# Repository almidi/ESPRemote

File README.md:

# ESPRemote
### VER 0.1

A simple WiFI remote controller using the ESP8266 SoC.

The goal of this project is the creation of a simple to use WiFi remote controller aimed at usage with the numerous home automation suites available, such as _[HomeAssistant](https://www.home-assistant.io)_ and _[OpenHab](https://www.openhab.org)_.

The system utilizes an _[Espressif ESP-12](https://docs.platformio.org/en/latest/boards/espressif8266/esp12e.html)_ module coupled with an _[MCP73831T](https://www.google.gr/url?sa=t&rct=j&q=&esrc=s&source=web&cd=1&ved=2ahUKEwiDvMTDpvbgAhXJfFAKHZEMD0UQFjAAegQIChAC&url=https%3A%2F%2Fwww.sparkfun.com%2Fdatasheets%2FPrototyping%2FBatteries%2FMCP73831T.pdf&usg=AOvVaw3YKAY2DJq01YtSUwFzsNai)_ chip for battery management and an _[AP2112K](https://www.google.gr/url?sa=t&rct=j&q=&esrc=s&source=web&cd=1&ved=2ahUKEwjnxLrnpvbgAhUEK1AKHWMBD-AQFjAAegQIChAC&url=https%3A%2F%2Fwww.diodes.com%2Fassets%2FDatasheets%2FAP2112.pdf&usg=AOvVaw2XV2W1VE0JfD3LlF0lkARI)_ LDO voltage regulator.

## Configurations

The board can be configured as a battery powered remote control, or as a DC powered button panel. To achieve this a jumper was added (SJ2) to select between battery and direct USB power. A second jumper was also added (JP2) to bypass the power switch. Using the above jumpers, the BMS circuit can be completely ignored and left unpopulated in case the device is inteded for always pluged-in use from a 5V DC power supply.

## Firmware

Using the _[Espressif ESP-12](https://docs.platformio.org/en/latest/boards/espressif8266/esp12e.html)_ module offers great flexibility in existing firmware options. Currently the _[ESPHome](https://esphome.io/index.html)_ firmware is used, designed for seemless intergation with the _[HomeAssistant](https://www.home-assistant.io)_ platform.

Due to the device not beign intended as a development board, an FTDI chip was excluded from the design, leaving the need for a small 6-pin SH 1.0mm micro jst connector as a UART interface.

**Uploading new firmware requires the pin D0 and GND of the UART connector to be tied together.** After doing so the device must be reset, setting it in download mode and enabling new firmware to be uploaded. **This can also be achieved holding down the 4th button before powering on the device**.

## I/O

|                 | Pin    |
|-----------------|--------|
| Button 1        | GPIO5  |
| Button 2        | GPIO4  |
| Button 3        | GPIO12 |
| Button 4        | GPIO0  |
| Button 5        | GPIO13 |
| Battery Voltage | ADC    |
| Status Led      | GPIO16 |

## PCB

## Enclosure

The enclosure is designed to incorporate a single 400mAh li-po cell and be 3D printed in two parts.

## Future Work

- Incorporate a small 128x64 OLED screen.
- Add an IR transmitter to the design, so that the controller can be used with existing household devices.
- Add an accelerometer for gesture control.
- Design a better, prettier and easier to hold enclosure.

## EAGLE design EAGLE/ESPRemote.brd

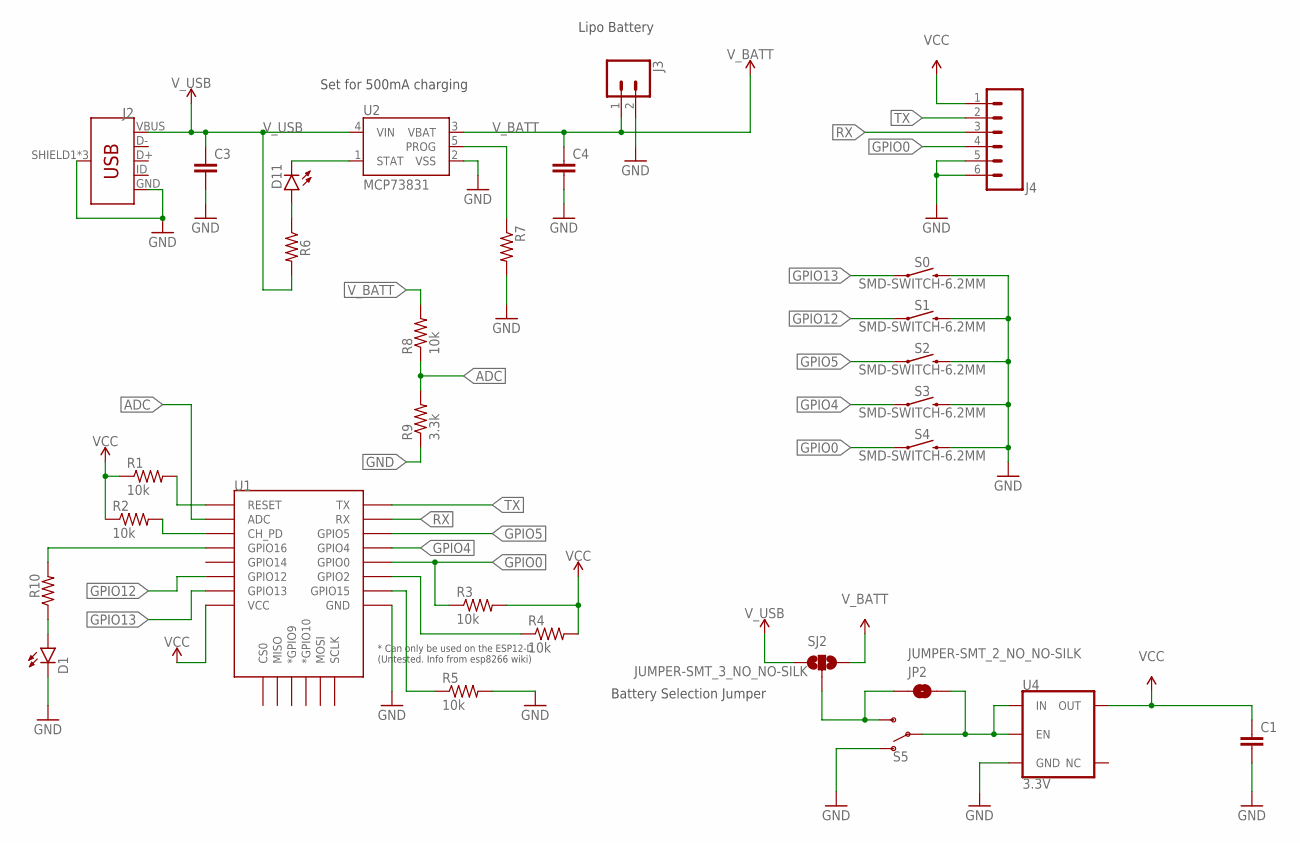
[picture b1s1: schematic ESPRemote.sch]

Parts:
C1, C3, C4: 10UF; C0603
D1: BLUE; CHIP-LED0805
D11: RED; CHIP-LED0805
J2: USB_MICRO-B_FEMALE-SMT; USB-B-MICRO-SMD
J3: CONN_02; 1X02
J4: CONN_06SMD-1MM; 1X06-1MM
JP2: JUMPER-SMT_2_NO_NO-SILK; SMT-JUMPER_2_NO_NO-SILK
R1, R2, R3, R4, R5, R8: 10k; R1206
R6: 1k; R1206
R7: 2.0k; R1206
R9: 3.3k; R1206
R10: 330; R1206
S0, S1, S2, S3, S4: SMD-SWITCH-6.2MM; TACTILE_SWITCH_SMD_6.0X3.5MM
S5: SWITCH-SPDT-SMD-RIGHT-ANGLE; SWITCH_SPST_SMD_A
SJ2: JUMPER-SMT_3_NO_NO-SILK; SMT-JUMPER_3_NO_NO-SILK
U1: ESP12ESMD; ESP12E-SMD
U2: MCP73831; SOT23-5
U4: 3.3V; SOT23-5

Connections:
ADC: R8.1, R9.2, U1.ADC
GND: C1.2, C3.2, C4.2, D1.C, J2.GND, J2.SHIELD1 (SHIELD), J2.SHIELD2 (SHIELD), J2.SHIELD3 (SHIELD), J3.2, J4.5, J4.6, R5.2, R7.2, R9.1, S0.2, S1.2, S2.2, S3.2, S4.2, S5.1 (O), U1.GND, U2.2 (VSS), U4.2 (GND)
GPIO0: J4.4, R3.1, S4.1, U1.GPIO0
GPIO4: S3.1, U1.GPIO4
GPIO5: S2.1, U1.GPIO5
GPIO12: S1.1, U1.GPIO12
GPIO13: S0.1, U1.GPIO13
unnamed: JP2.2, S5.2, U4.1 (IN), U4.3 (EN)
unnamed: R1.2, U1.RESET
unnamed: D11.A, R6.1
unnamed: R2.2, U1.CH_PD
unnamed: R4.1, U1.GPIO2
unnamed: JP2.1, S5.3 (S), SJ2.2
unnamed: R5.1, U1.GPIO15
unnamed: R10.2, U1.GPIO16
unnamed: D1.A, R10.1
PROG: R7.1, U2.5 (PROG)
RX: J4.3, U1.RXD0 (RX)
STAT: D11.C, U2.1 (STAT)
TX: J4.2, U1.TXD0 (TX)
VCC: C1.1, J4.1, R1.1, R2.1, R3.2, R4.2, U1.VCC, U4.5 (OUT)
V_BATT: C4.1, J3.1, R8.2, SJ2.3, U2.3 (VBAT)
V_USB: C3.1, J2.VBUS, R6.2, SJ2.1, U2.4 (VIN)

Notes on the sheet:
Set for 500mA charging
Battery Selection Jumper
Lipo Battery

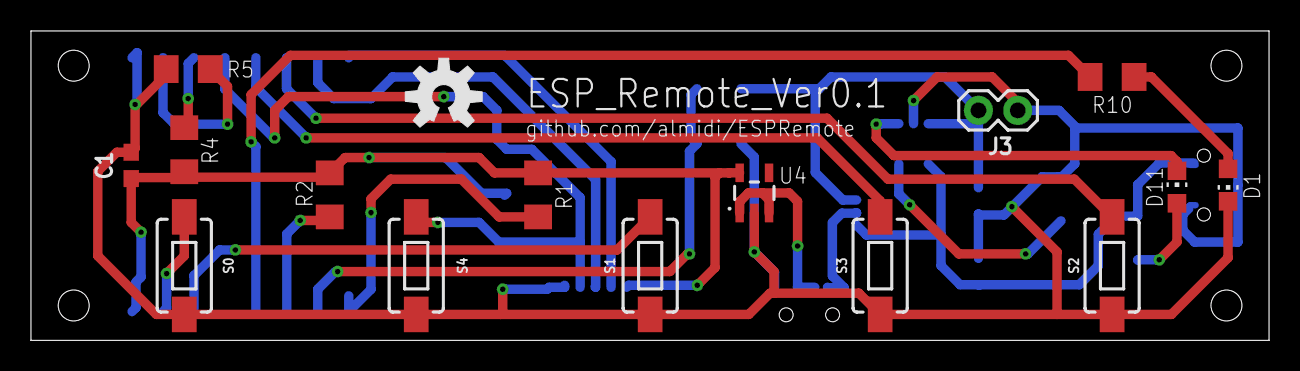
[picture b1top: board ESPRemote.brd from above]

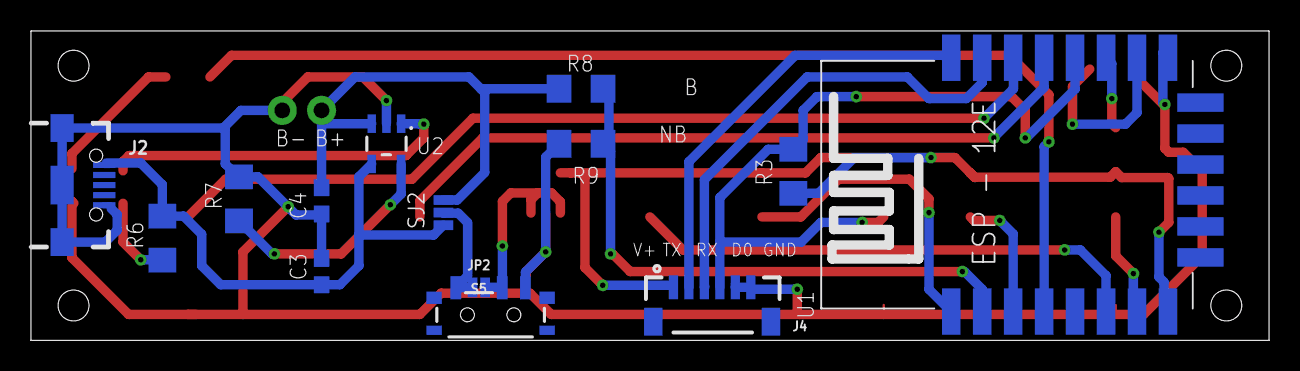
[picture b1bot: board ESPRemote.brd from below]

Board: 2 copper layers, 80.0 x 20.0 mm, 30 parts (14 on the bottom side), 23 nets.

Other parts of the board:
U$2: OSHW-LOGO-M

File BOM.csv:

"Part";"Value";"Device";"Package";"Description";"PROD_ID";"SF_ID";"SF_SKU";"SPICEPREFIX";"VALUE";
"C1";"10UF";"10UF";"C0603";"10.0µF ceramic capacitors";"";"";"";"";"";
"C3";"10UF";"10UF";"C0603";"10.0µF ceramic capacitors";"";"";"";"";"";
"C4";"10UF";"10UF";"C0603";"10.0µF ceramic capacitors";"";"";"";"";"";
"D1";"BLUE";"LEDCHIP-LED0805";"CHIP-LED0805";"LED";"";"";"";"";"";
"D11";"RED";"LEDCHIP-LED0805";"CHIP-LED0805";"LED";"";"";"";"";"";
"J2";"";"USB_MICRO-B_FEMALE-SMT";"USB-B-MICRO-SMD";"USB Type Micro-B Connector";"CONN-11752";"";"";"";"";
"J3";"";"CONN_02";"1X02";"Multi connection point. Often used as Generic Header-pin footprint for 0.1 inch spaced/style header connections";"";"";"";"";"";
"J4";"";"CONN_06SMD-1MM";"1X06-1MM";"Multi connection point. Often used as Generic Header-pin footprint for 0.1 inch spaced/style header connections";"CONN-08249";"GPS-00579";"";"";"";
"JP2";"JUMPER-SMT_2_NO_NO-SILK";"JUMPER-SMT_2_NO_NO-SILK";"SMT-JUMPER_2_NO_NO-SILK";"Normally open jumper";"";"";"";"";"";
"R1";"10k";"R-US_R1206";"R1206";"RESISTOR, American symbol";"";"";"";"";"";
"R2";"10k";"R-US_R1206";"R1206";"RESISTOR, American symbol";"";"";"";"";"";
"R3";"10k";"R-US_R1206";"R1206";"RESISTOR, American symbol";"";"";"";"";"";
"R4";"10k";"R-US_R1206";"R1206";"RESISTOR, American symbol";"";"";"";"";"";
"R5";"10k";"R-US_R1206";"R1206";"RESISTOR, American symbol";"";"";"";"";"";
"R6";"330";"R-US_R1206";"R1206";"RESISTOR, American symbol";"";"";"";"";"";
"R7";"2.0k";"R-US_R1206";"R1206";"RESISTOR, American symbol";"";"";"";"";"";
"R8";"10k";"R-US_R1206";"R1206";"RESISTOR, American symbol";"";"";"";"";"";
"R9";"10k";"R-US_R1206";"R1206";"RESISTOR, American symbol";"";"";"";"";"";
"R10";"330";"R-US_R1206";"R1206";"RESISTOR, American symbol";"";"";"";"";"";
"S0";"SMD-SWITCH-6.2MM";"MOMENTARY-SWITCH-SPST-SMD-6.0X3.5MM";"TACTILE_SWITCH_SMD_6.0X3.5MM";"Momentary Switch (Pushbutton) - SPST";"SWCH-00815";"";"COM-08229";"";"";
"S1";"SMD-SWITCH-6.2MM";"MOMENTARY-SWITCH-SPST-SMD-6.0X3.5MM";"TACTILE_SWITCH_SMD_6.0X3.5MM";"Momentary Switch (Pushbutton) - SPST";"SWCH-00815";"";"COM-08229";"";"";
"S2";"SMD-SWITCH-6.2MM";"MOMENTARY-SWITCH-SPST-SMD-6.0X3.5MM";"TACTILE_SWITCH_SMD_6.0X3.5MM";"Momentary Switch (Pushbutton) - SPST";"SWCH-00815";"";"COM-08229";"";"";
"S3";"SMD-SWITCH-6.2MM";"MOMENTARY-SWITCH-SPST-SMD-6.0X3.5MM";"TACTILE_SWITCH_SMD_6.0X3.5MM";"Momentary Switch (Pushbutton) - SPST";"SWCH-00815";"";"COM-08229";"";"";
"S4";"SMD-SWITCH-6.2MM";"MOMENTARY-SWITCH-SPST-SMD-6.0X3.5MM";"TACTILE_SWITCH_SMD_6.0X3.5MM";"Momentary Switch (Pushbutton) - SPST";"SWCH-00815";"";"COM-08229";"";"";
"S5";"";"SWITCH-SPDT-SMD-RIGHT-ANGLE";"SWITCH_SPST_SMD_A";"Single Pole, Double Throw (SPDT) Switch";"SWCH-10651";"";"COM-10860";"";"";
"SJ2";"JUMPER-SMT_3_NO_NO-SILK";"JUMPER-SMT_3_NO_NO-SILK";"SMT-JUMPER_3_NO_NO-SILK";"Normally open jumper";"";"";"";"";"";
"U1";"";"ESP12ESMD";"ESP12E-SMD";"ESP12E Module";"";"";"";"X";"";
"U2";"MCP73831";"MCP73831";"SOT23-5";"MCP73831T Li-Ion, Li-Pol Controller";"IC-09995";"";"";"";"";
"U4";"3.3V";"V_REG_AP2112K-3.3V";"SOT23-5";"AP2112 - 600mA CMOS LDO Regulator w/ Enable";"VREG-12457";"";"";"";"3.3V";

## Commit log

2019-03-04 Init
2019-04-27 Added ESPHome Configuration
2019-04-27 Updated Enclosures
2022-03-26 v2 enclosure
2022-03-26 image

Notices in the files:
parts and their libraries:
SparkFun-Capacitors: Licensing: Creative Commons ShareAlike 4.0 International - https://creativecommons.org/licenses/by-sa/4.0
